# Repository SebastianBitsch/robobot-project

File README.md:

### Getting started

1. Connect to robot 
  ```bash
  ssh local@10.197.216.74
  ```

2. Login
  ```password: grenen```

3. Build
  ```bash
  cd svn/robobot/raubase/build && make
  ```

4. Run
  ```bash
  cd svn/robobot/raubase/build && ./raubase
  ```

### Tips and tricks
- Moving files from ```ssh``` to ```local```. On a terminal on your local machine: 
  ```bash
  scp -r local@10.197.216.74:/home/local/svn<PATH_TO_FILE> <LOCAL_PATH>
  ```
  - For instance:
  ```bash
  scp -r local@10.197.216.74:/home/local/svn/robobot/raubase/build/img/ /Users/sebastianbitsch/Desktop/
  ```

# Camera
Access the stream
```bash
cd svn/robobot/raubase/build/
motion
```
See the output stream at <http://10.197.216.74:8081>

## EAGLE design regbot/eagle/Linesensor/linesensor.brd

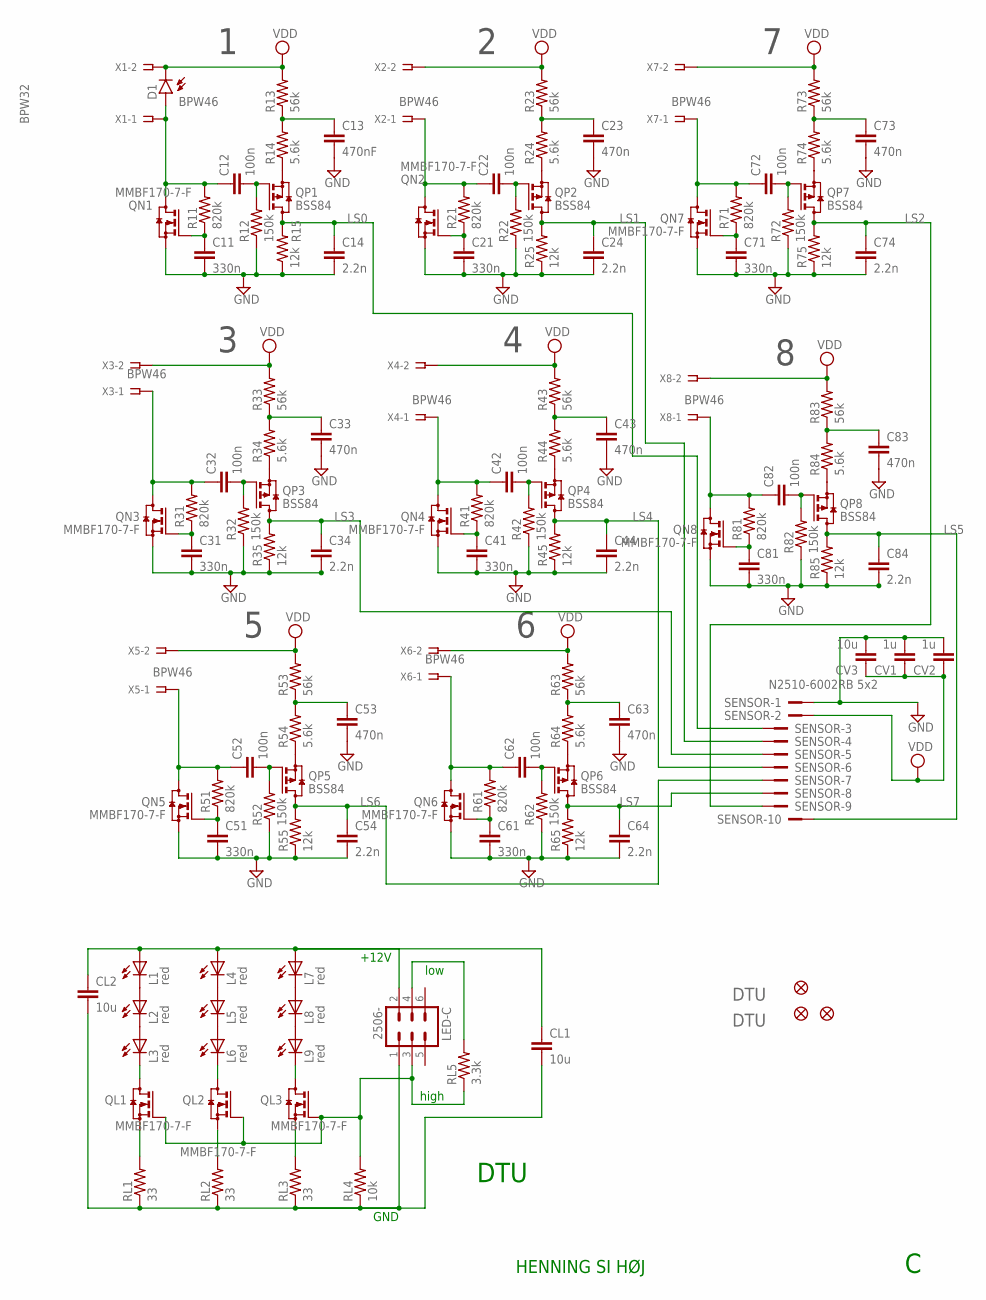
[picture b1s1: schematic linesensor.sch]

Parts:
C11, C21, C31, C41, C51, C61, C71, C81: 330n; 0805
C12, C22, C32, C42, C52, C62, C72, C82: 100n; 0805
C13: 470nF; 0805
C14, C24, C34, C44, C54, C64, C74, C84: 2.2n; 0805
C23, C33, C43, C53, C63, C73, C83: 470n; 0805
CL1, CL2: 10u; 1210
CV1, CV2: 1u; 0805
CV3: 10u; 1210
D1: BPW32
FD1, FD2, FD3: FIDUCIAL1X2; FIDUCIAL-1X2
L1, L2, L3, L4, L5, L6, L7, L8, L9: red; LED3MM
LED-C: 2506-; PAK100/2500-06
QL1, QL2, QL3: MMBF170-7-F; SOT23
QN1, QN2, QN3, QN4, QN5, QN6, QN7, QN8: MMBF170-7-F; SOT23
QP1, QP2, QP3, QP4, QP5, QP6, QP7, QP8: BSS84; SOT23
R11, R21, R31, R41, R51, R61, R71, R81: 820k; 0805
R12, R22, R32, R42, R52, R62, R72, R82: 150k; 0805
R13, R23, R33, R43, R53, R63, R73, R83: 56k; 0805
R14, R24, R34, R44, R54, R64, R74, R84: 5.6k; 0805
R15, R25, R35, R45, R55, R65, R75, R85: 12k; 0805
RL1, RL2, RL3: 33; 0805
RL4: 10k; 0805
RL5: 3.3k; 0805
SENSOR: N2510-6002RB 5x2; PAK100/2500-10
U$1: DTUSMALL-5MM; DTU-SMALL-5MM
U$2: DTULARGE; DTU-LARGE
X1, X2, X3, X4, X5, X6, X7, X8: BPW46; SSW-102-02-S-S

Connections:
GATE_CTRL: LED-C.3, QL1.1 (G), QL2.1 (G), QL3.1 (G), RL4.2, RL5.1
GND: C11.2, C13.2, C14.2, C21.2, C23.2, C24.2, C31.2, C33.2, C34.2, C41.2, C43.2, C44.2, C51.2, C53.2, C54.2, C61.2, C63.2, C64.2, C71.2, C73.2, C74.2, C81.2, C83.2, C84.2, CV1.2, CV2.2, CV3.2, QN1.2 (S), QN2.2 (S), QN3.2 (S), QN4.2 (S), QN5.2 (S), QN6.2 (S), QN7.2 (S), QN8.2 (S), R12.1, R15.1, R22.1, R25.1, R32.1, R35.1, R42.1, R45.1, R52.1, R55.1, R62.1, R65.1, R72.1, R75.1, R82.1, R85.1, SENSOR.1
GND2: CL1.2, CL2.2, LED-C.1, RL1.1, RL2.1, RL3.1, RL4.1
LS0: C14.1, QP1.3 (D), R15.2, SENSOR.3
LS1: C24.1, QP2.3 (D), R25.2, SENSOR.4
LS2: C74.1, QP7.3 (D), R75.2, SENSOR.9
LS3: C34.1, QP3.3 (D), R35.2, SENSOR.5
LS4: C44.1, QP4.3 (D), R45.2, SENSOR.6
LS5: C84.1, QP8.3 (D), R85.2, SENSOR.10
LS6: C54.1, QP5.3 (D), R55.2, SENSOR.7
LS7: C64.1, QP6.3 (D), R65.2, SENSOR.8
unnamed: QP1.2 (S), R14.1
unnamed: QP2.2 (S), R24.1
unnamed: C11.1, QN1.1 (G), R11.1
unnamed: C12.1, D1.A, QN1.3 (D), R11.2, X1.1
unnamed: C12.2, QP1.1 (G), R12.2
unnamed: L1.K (C), L2.A
unnamed: C13.1, R13.1, R14.2
unnamed: C21.1, QN2.1 (G), R21.1
unnamed: C22.1, QN2.3 (D), R21.2, X2.1
unnamed: C22.2, QP2.1 (G), R22.2
unnamed: L2.K (C), L3.A
unnamed: C23.1, R23.1, R24.2
unnamed: QP3.2 (S), R34.1
unnamed: C31.1, QN3.1 (G), R31.1
unnamed: C32.1, QN3.3 (D), R31.2, X3.1
unnamed: C32.2, QP3.1 (G), R32.2
unnamed: L4.K (C), L5.A
unnamed: C33.1, R33.1, R34.2
unnamed: QP4.2 (S), R44.1
unnamed: C41.1, QN4.1 (G), R41.1
unnamed: C42.1, QN4.3 (D), R41.2, X4.1
unnamed: C42.2, QP4.1 (G), R42.2
unnamed: L5.K (C), L6.A
unnamed: C43.1, R43.1, R44.2
unnamed: QP5.2 (S), R54.1
unnamed: C51.1, QN5.1 (G), R51.1
unnamed: C52.1, QN5.3 (D), R51.2, X5.1
unnamed: C52.2, QP5.1 (G), R52.2
unnamed: L7.K (C), L8.A
unnamed: C53.1, R53.1, R54.2
unnamed: QP6.2 (S), R64.1
unnamed: C61.1, QN6.1 (G), R61.1
unnamed: C62.1, QN6.3 (D), R61.2, X6.1
unnamed: C62.2, QP6.1 (G), R62.2
unnamed: L8.K (C), L9.A
unnamed: C63.1, R63.1, R64.2
unnamed: QP7.2 (S), R74.1
unnamed: C71.1, QN7.1 (G), R71.1
unnamed: C72.1, QN7.3 (D), R71.2, X7.1
unnamed: C72.2, QP7.1 (G), R72.2
unnamed: L3.K (C), QL1.3 (D)
unnamed: C73.1, R73.1, R74.2
unnamed: QP8.2 (S), R84.1
unnamed: C81.1, QN8.1 (G), R81.1
unnamed: C82.1, QN8.3 (D), R81.2, X8.1
unnamed: C82.2, QP8.1 (G), R82.2
unnamed: L6.K (C), QL2.3 (D)
unnamed: C83.1, R83.1, R84.2
unnamed: L9.K (C), QL3.3 (D)
unnamed: QL1.2 (S), RL1.2
unnamed: QL2.2 (S), RL2.2
unnamed: QL3.2 (S), RL3.2
unnamed: LED-C.4, RL5.2
VDD: CV1.1, CV2.1, CV3.1, D1.K (C), R13.2, R23.2, R33.2, R43.2, R53.2, R63.2, R73.2, R83.2, SENSOR.2, X1.2, X2.2, X3.2, X4.2, X5.2, X6.2, X7.2, X8.2
VDD2: CL1.1, CL2.1, L1.A, L4.A, L7.A, LED-C.2

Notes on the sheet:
DTU
HENNING SI HØJ
+12V
GND
low
high

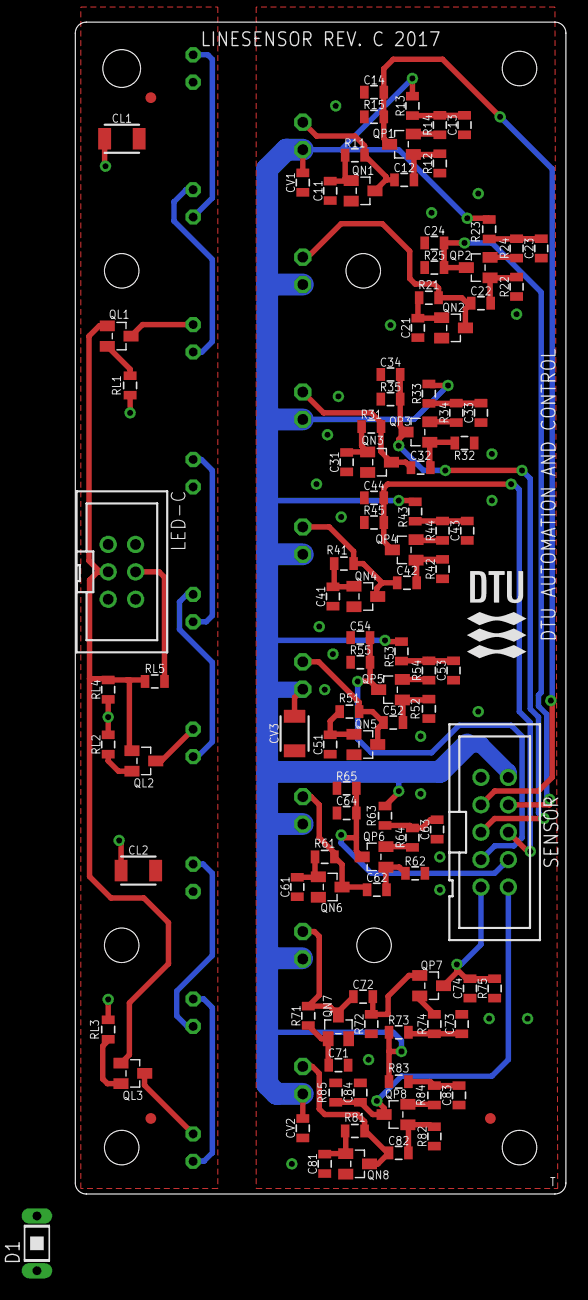
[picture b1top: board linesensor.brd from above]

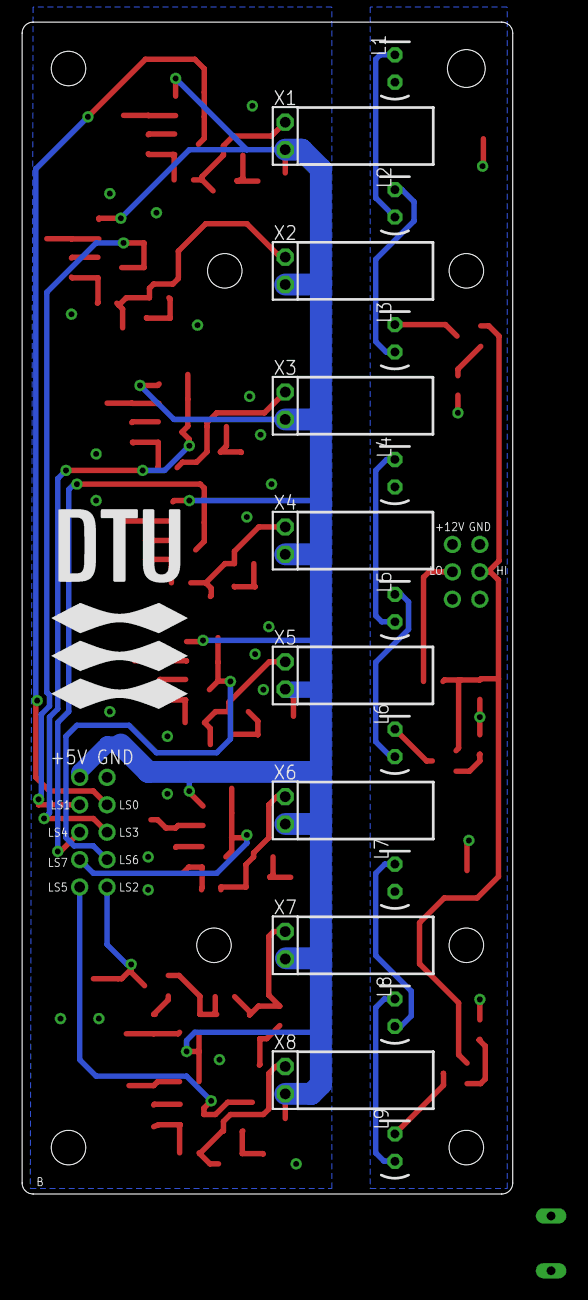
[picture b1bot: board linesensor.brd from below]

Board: 2 copper layers, 45.5 x 108.6 mm, 126 parts (18 on the bottom side), 66 nets.

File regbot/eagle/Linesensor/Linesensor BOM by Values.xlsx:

No. | part number/description | Package | Value | Qty | RefDefs | Note
1 |  | C0805 | 100nF/50V | 8 | C12, C22, C32, C42, C52, C62, C72, C82
2 |  | R0805 | 10k/1% | 1 | RL4
3 |  | C1210 | 10uF/50V | 3 | CL1, CL2, CV3
4 |  | R0805 | 12k/1% | 8 | R15, R25, R35, R45, R55, R65, R75, R85
5 |  | R0805 | 150k/1% | 8 | R12, R22, R32, R42, R52, R62, R72, R82
6 |  | C0805 | 1uF/50V | 2 | CV1, CV2
7 |  | C0805 | 2.2nF/50V | 8 | C14, C24, C34, C44, C54, C64, C74, C84
8 |  | R0805 | 3.3k/1% | 1 | RL5
9 |  | R0805 | 33R/1% | 3 | RL1, RL2, RL3
10 |  | C0805 | 330nF/50V | 8 | C11, C21, C31, C41, C51, C61, C71, C81
11 |  | C0805 | 470nF/50V | 8 | C13, C23, C33, C43, C53, C63, C73, C83
12 |  | R0805 | 5.6k/1% | 8 | R14, R24, R34, R44, R54, R64, R74, R84
13 |  | R0805 | 56k/1% | 8 | R13, R23, R33, R43, R53, R63, R73, R83
14 |  | R0805 | 820k/1% | 8 | R11, R21, R31, R41, R51, R61, R71, R81
15 |  | SOT23 | BSS84 | 8 | QP1, QP2, QP3, QP4, QP5, QP6, QP7, QP8
16 |  | SOT23 | MMBF170 | 11 | QL1, QL2, QL3, QN1, QN2, QN3, QN4, QN5, QN6, QN7, QN8
 | PCBWay PCB Assembly Service

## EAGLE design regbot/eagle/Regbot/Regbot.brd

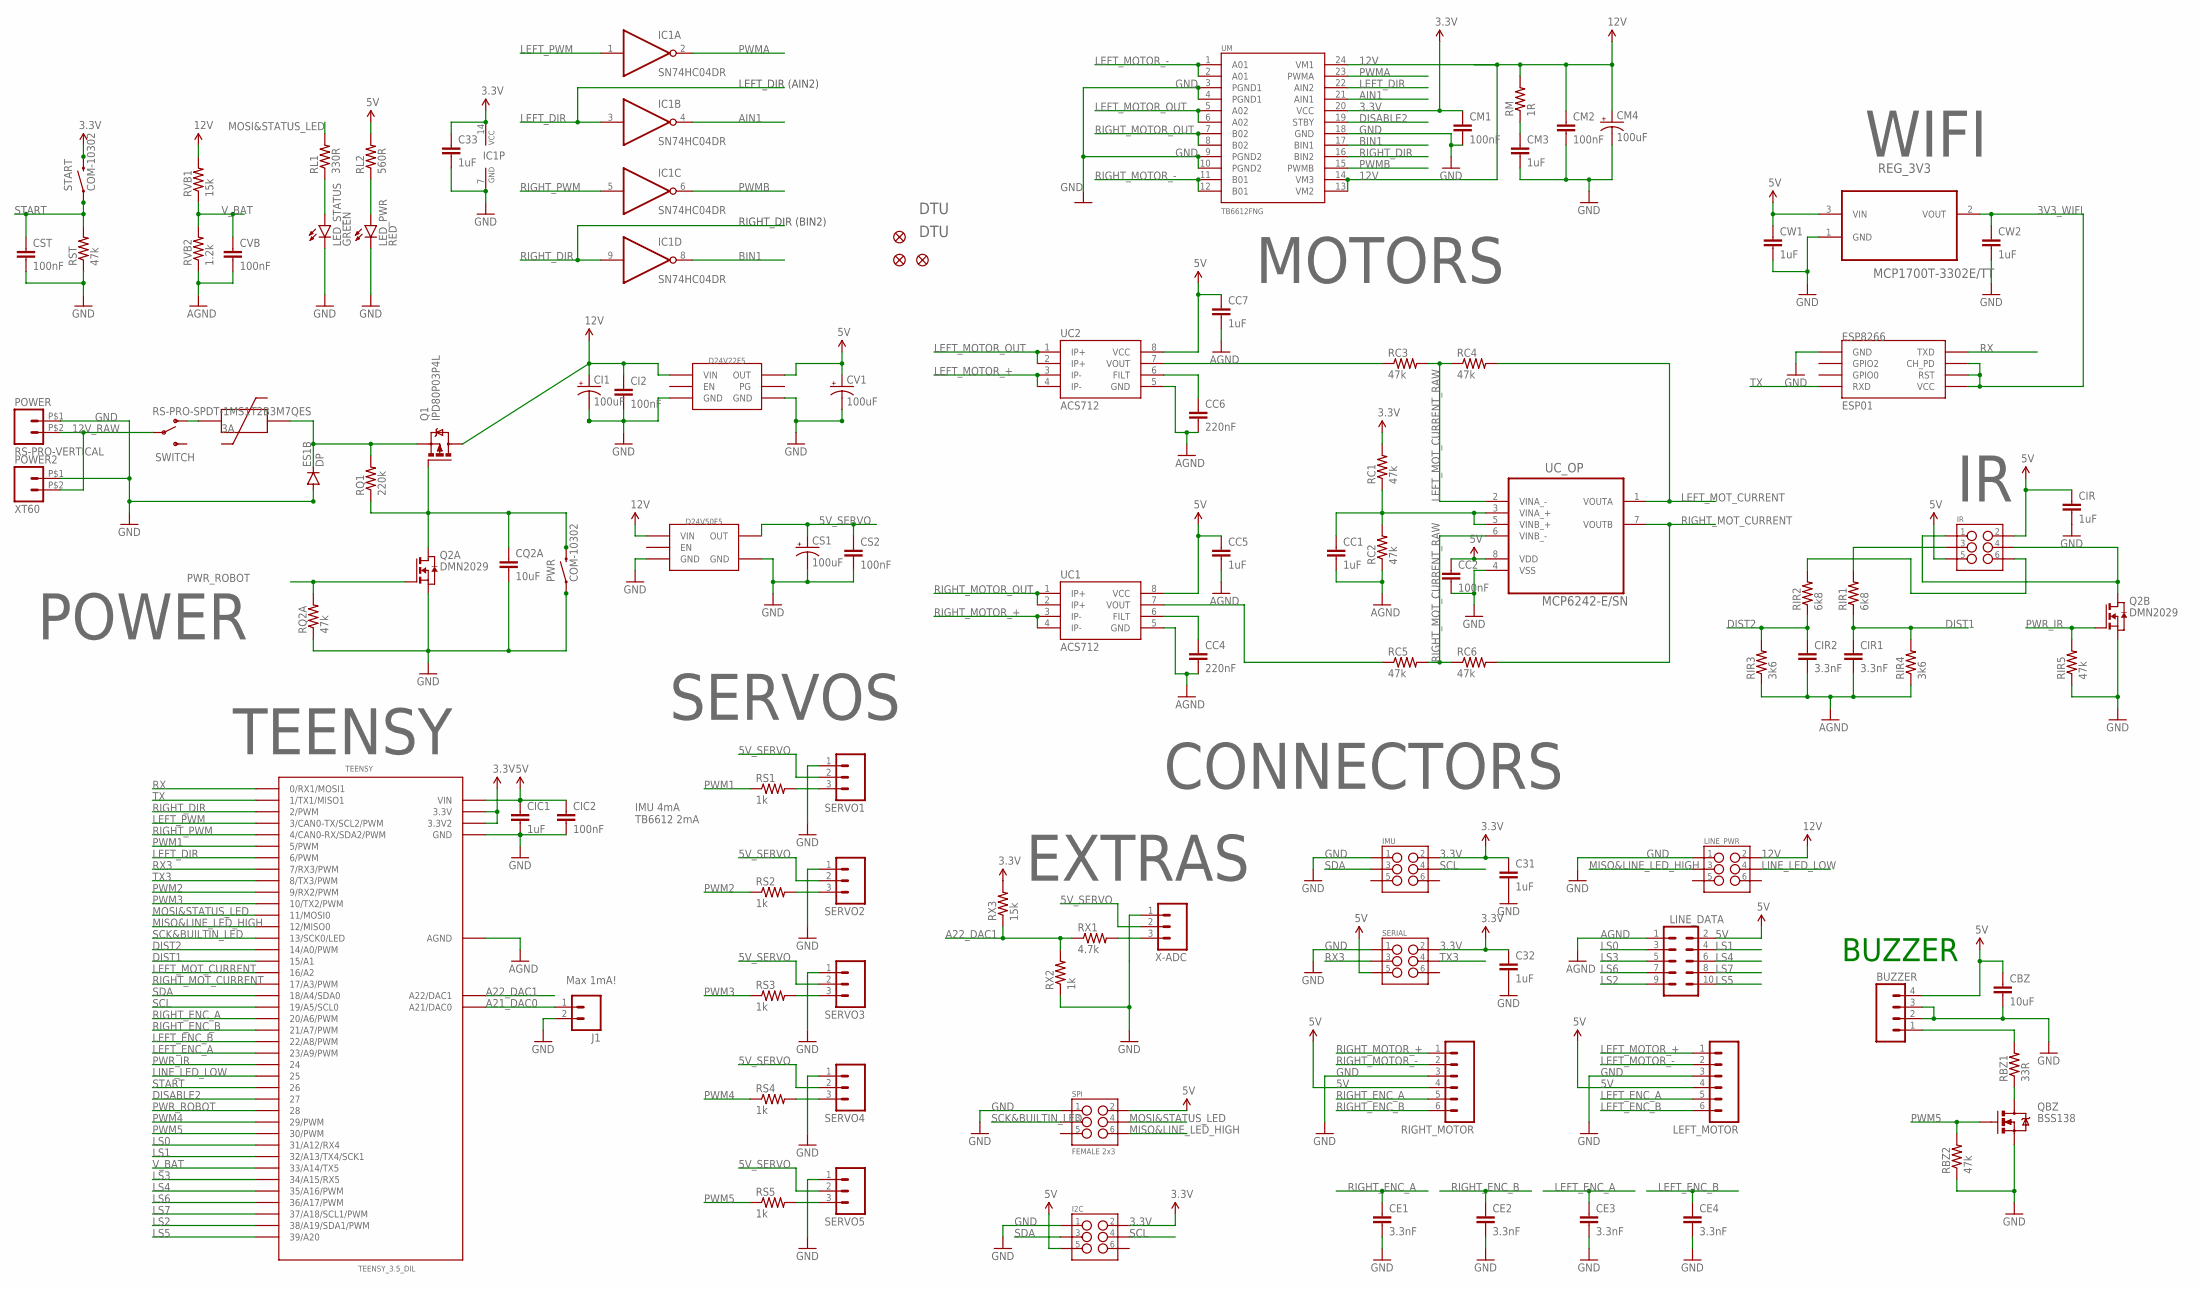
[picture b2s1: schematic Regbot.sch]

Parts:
BUZZER: M04POLAR; MOLEX-1X4
C31, C32, C33: 1uF; 0805
CBZ: 10uF; 1210
CC1, CC5, CC7: 1uF; 0805
CC2: 100nF; 0805
CC4, CC6: 220nF; 0805
CE1, CE2, CE3, CE4: 3.3nF; 0805
CI1: 100uF; PANASONIC_D_XL
CI2: 100nF; 0805
CIC1: 1uF; 0805
CIC2: 100nF; 0805
CIR: 1uF; 0805
CIR1, CIR2: 3.3nF; 0805
CM1, CM2: 100nF; 0805
CM3: 1uF; 0805
CM4: 100uF; PANASONIC_D_XL
CQ2A: 10uF; 1210
CS1: 100uF; PANASONIC_D_XL
CS2: 100nF; 0805
CST: 100nF; 0805
CV1: 100uF; PANASONIC_D_XL
CVB: 100nF; 0805
CW1, CW2: 1uF; 0805
D24V22F5: POLOLU_D24V22; D24V22
D24V50F5: POLOLU_D24V50; D24V50
DP: ES1B; SMA-DIODE
ESP8266: ESP01
FD1, FD2, FD3: FIDUCIAL1X2; FIDUCIAL-1X2
I2C: M03X2SHROUD; 2X3-SHROUDED
IC1: SN74HC04DR; SO14
IMU: M03X2SHROUD; 2X3-SHROUDED
IR: M03X2SHROUD; 2X3-SHROUDED
J1: M02PTH; 1X02
LED_PWR: RED; LED-1206
LED_STATUS: GREEN; LED-1206
LEFT_MOTOR: M06SILK_FEMALE_PTH; 1X06
LINE_DATA: M05X2SHD; 2X5-SHROUDED
LINE_PWR: M03X2SHROUD; 2X3-SHROUDED
MAIN_FUSE: SMF_OMNI-BLOK_FUSE_BLOCK
POWER: RS-PRO-VERTICAL
POWER2: XT60
PWR: COM-10302; TACTILE-PTH-12MM
Q1: IPD80P03P4L; D-PAK_TO252AA
Q2: DMN2029; SO8
QBZ: BSS138; SOT23
RBZ1: 33R; 0805
RBZ2: 47k; 0805
RC1, RC2, RC3, RC4, RC5, RC6: 47k; 0805
REG_3V3: MCP1700T-3302E/TT; SOT95P237X112-3N
RIGHT_MOTOR: M06SILK_FEMALE_PTH; 1X06
RIR1, RIR2: 6k8; 0805
RIR3, RIR4: 3k6; 0805
RIR5: 47k; 0805
RL1: 330R; 0805
RL2: 560R; 0805
RM: 1R; 0805
RQ1: 220k; 0805
RQ2A: 47k; 0805
RS1, RS2, RS3, RS4, RS5: 1k; 0805
RST: 47k; 0805
RVB1: 15k; 0805
RVB2: 1.2k; 0805
RX1: 4.7k; 0805
RX2: 1k; 0805
RX3: 15k; 0805
SERIAL: M03X2SHROUD; 2X3-SHROUDED
SERVO1, SERVO2, SERVO3, SERVO4, SERVO5: M03POLAR; MOLEX-1X3
SPI: FEMALE 2x3; 2X3
START: COM-10302; TACTILE-PTH-12MM
SWITCH: RS-PRO-SPDT-1MS1T2B3M7QES; RS-PRO-1MS1T2B3M7QES
TEENSY: TEENSY_3.5_DIL
U$1: DTUMEDIUM-9MM; DTU-MEDIUM-9MM
U$2: DTULARGE; DTU-LARGE
UC1, UC2: ACS712; SO08
UC_OP: MCP6242-E/SN; SOIC127P600X175-8N
UM: TB6612FNG; SSOP24
X-ADC: M03POLAR; MOLEX-1X3

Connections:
3.3V: C31.1, C32.1, C33.1, CM1.1, I2C.2, IC1.14 (VCC), IMU.2, RC1.2, RX3.2, SERIAL.2, START.3, START.4, TEENSY.3.3V, TEENSY.3.3V3 (3.3V2), UM.20 (VCC)
3V3_WIFI: CW2.1, ESP8266.CH_PD, ESP8266.RST, ESP8266.VCC, REG_3V3.2 (VOUT)
5V: BUZZER.4, CBZ.1, CC2.1, CC5.1, CC7.1, CIC1.1, CIC2.1, CIR.1, CV1.+, CW1.1, D24V22F5.P$OUT (OUT), I2C.5, IR.2, IR.5, LEFT_MOTOR.4, LINE_DATA.2, REG_3V3.3 (VIN), RIGHT_MOTOR.4, RL2.2, SERIAL.5, SPI.2, TEENSY.VIN, UC1.8 (VCC), UC2.8 (VCC), UC_OP.8 (VDD)
5V_SERVO: CS1.+, CS2.1, D24V50F5.P$OUT (OUT), SERVO1.2, SERVO2.2, SERVO3.2, SERVO4.2, SERVO5.2, X-ADC.2
12V: CI1.+, CI2.1, CM2.1, CM4.+, D24V22F5.P$VIN (VIN), D24V50F5.P$VIN (VIN), LINE_PWR.2, Q1.4 (D), RM.2, RVB1.2, UM.13 (VM2), UM.14 (VM3), UM.24 (VM1)
12V_RAW: POWER.P$2 (2), POWER2.P$2 (2), SWITCH.P$2 (P2)
A21_DAC0: J1.1, TEENSY.A21 (A21/DAC0)
A22_DAC1: RX1.1, RX2.2, RX3.1, TEENSY.A22 (A22/DAC1)
AGND: CC1.2, CC4.2, CC5.2, CC6.2, CC7.2, CIR1.2, CIR2.2, CVB.2, LINE_DATA.1, RC2.1, RIR3.1, RIR4.1, RVB2.1, TEENSY.AGND, UC1.5 (GND), UC2.5 (GND)
AIN1: IC1.4 (O), UM.21 (AIN1)
BIN1: IC1.8 (O), UM.17 (BIN1)
DISABLE2: TEENSY.27, UM.19 (STBY)
DIST1: CIR1.1, RIR1.1, RIR4.2, TEENSY.15/A1
DIST2: CIR2.1, RIR2.1, RIR3.2, TEENSY.14/A0 (14/A0/PWM)
GND: BUZZER.2, BUZZER.3, C31.2, C32.2, C33.2, CBZ.2, CC2.2, CE1.2, CE2.2, CE3.2, CE4.2, CI1.-, CI2.2, CIC1.2, CIC2.2, CIR.2, CM1.2, CM2.2, CM3.2, CM4.-, CQ2A.2, CS1.-, CS2.2, CST.2, CV1.-, CW1.2, CW2.2, D24V22F5.P$GND1 (GND), D24V22F5.P$GND2 (GND2), D24V50F5.P$GND (GND), D24V50F5.P$GND2 (GND2), DP.A, ESP8266.GND, I2C.1, IC1.7 (GND), IMU.1, J1.2, LED_PWR.C, LED_STATUS.C, LEFT_MOTOR.3, LINE_PWR.1, POWER.P$1 (1), POWER2.P$1 (1), PWR.1, PWR.2, Q2.1 (S), Q2.3 (S), QBZ.2 (S), RBZ2.1, REG_3V3.1 (GND), RIGHT_MOTOR.3, RIR5.1, RQ2A.1, RST.1, RX2.1, SERIAL.1, SERVO1.1, SERVO2.1, SERVO3.1, SERVO4.1, SERVO5.1, SPI.1, TEENSY.GND, TEENSY.GND1 (GND), UC_OP.4 (VSS), UM.3 (PGND1), UM.4 (PGND1), UM.9 (PGND2), UM.10 (PGND2), UM.18 (GND), X-ADC.1
LEFT_DIR: IC1.3 (I), TEENSY.6 (6/PWM), UM.22 (AIN2)
LEFT_ENC_A: CE3.1, LEFT_MOTOR.5, TEENSY.23/A9 (23/A9/PWM)
LEFT_ENC_B: CE4.1, LEFT_MOTOR.6, TEENSY.22/A8 (22/A8/PWM)
LEFT_MOTOR_+: LEFT_MOTOR.1, UC2.3 (IP-), UC2.4 (IP-)
LEFT_MOTOR_-: LEFT_MOTOR.2, UM.1 (A01), UM.2 (A01)
LEFT_MOTOR_OUT: UC2.1 (IP+), UC2.2 (IP+), UM.5 (A02), UM.6 (A02)
LEFT_MOT_CURRENT: RC4.2, TEENSY.16/A2, UC_OP.1 (VOUTA)
LEFT_MOT_CURRENT_RAW: RC3.2, RC4.1, UC_OP.2 (VINA_-)
LEFT_PWM: IC1.1 (I), TEENSY.3 (3/CAN0-TX/SCL2/PWM)
LINE_LED_LOW: LINE_PWR.4, TEENSY.25
LS0: LINE_DATA.3, TEENSY.31/A12 (31/A12/RX4)
LS1: LINE_DATA.4, TEENSY.32/A13 (32/A13/TX4/SCK1)
LS2: LINE_DATA.9, TEENSY.38/A19 (38/A19/SDA1/PWM)
LS3: LINE_DATA.5, TEENSY.34/A15 (34/A15/RX5)
LS4: LINE_DATA.6, TEENSY.35/A16 (35/A16/PWM)
LS5: LINE_DATA.10, TEENSY.39/A20
LS6: LINE_DATA.7, TEENSY.36/A17 (36/A17/PWM)
LS7: LINE_DATA.8, TEENSY.37/A18 (37/A18/SCL1/PWM)
MISO&LINE_LED_HIGH: LINE_PWR.3, SPI.6, TEENSY.12 (12/MISO0)
MOSI&STATUS_LED: RL1.2, SPI.4, TEENSY.11 (11/MOSI0)
unnamed: BUZZER.1, RBZ1.2
unnamed: QBZ.3 (D), RBZ1.1
unnamed: LED_STATUS.A, RL1.1
unnamed: LED_PWR.A, RL2.1
unnamed: DP.C, MAIN_FUSE.PIN1, Q1.3 (S), RQ1.2
unnamed: MAIN_FUSE.PIN2, SWITCH.P$1 (O1)
unnamed: CQ2A.1, PWR.3, PWR.4, Q1.1 (G), Q2.7 (D), Q2.8 (D), RQ1.1
unnamed: CM3.1, RM.1
unnamed: CC4.1, UC1.6 (FILT)
unnamed: CC6.1, UC2.6 (FILT)
unnamed: RC5.1, UC1.7 (VOUT)
unnamed: CC1.1, RC1.1, RC2.2, UC_OP.3 (VINA_+), UC_OP.5 (VINB_+)
unnamed: RC3.1, UC2.7 (VOUT)
unnamed: IR.1, IR.4, Q2.5 (D), Q2.6 (D)
unnamed: RS1.2, SERVO1.3
unnamed: IR.3, RIR1.2
unnamed: IR.6, RIR2.2
unnamed: RS2.2, SERVO2.3
unnamed: RS3.2, SERVO3.3
unnamed: RS4.2, SERVO4.3
unnamed: RS5.2, SERVO5.3
unnamed: RX1.2, X-ADC.3
PWM1: RS1.1, TEENSY.5 (5/PWM)
PWM2: RS2.1, TEENSY.9 (9/RX2/PWM)
PWM3: RS3.1, TEENSY.10 (10/TX2/PWM)
PWM4: RS4.1, TEENSY.29 (29/PWM)
PWM5: QBZ.1 (G), RBZ2.2, RS5.1, TEENSY.30 (30/PWM)
PWMA: IC1.2 (O), UM.23 (PWMA)
PWMB: IC1.6 (O), UM.15 (PWMB)
PWR_IR: Q2.4 (G), RIR5.2, TEENSY.24
PWR_ROBOT: Q2.2 (G), RQ2A.2, TEENSY.28
RIGHT_DIR: IC1.9 (I), TEENSY.2 (2/PWM), UM.16 (BIN2)
RIGHT_ENC_A: CE1.1, RIGHT_MOTOR.5, TEENSY.20/A6 (20/A6/PWM)
RIGHT_ENC_B: CE2.1, RIGHT_MOTOR.6, TEENSY.21/A7 (21/A7/PWM)
RIGHT_MOTOR_+: RIGHT_MOTOR.1, UC1.3 (IP-), UC1.4 (IP-)
RIGHT_MOTOR_-: RIGHT_MOTOR.2, UM.11 (B01), UM.12 (B01)
RIGHT_MOTOR_OUT: UC1.1 (IP+), UC1.2 (IP+), UM.7 (B02), UM.8 (B02)
RIGHT_MOT_CURRENT: RC6.2, TEENSY.17/A3 (17/A3/PWM), UC_OP.7 (VOUTB)
RIGHT_MOT_CURRENT_RAW: RC5.2, RC6.1, UC_OP.6 (VINB_-)
RIGHT_PWM: IC1.5 (I), TEENSY.4 (4/CAN0-RX/SDA2/PWM)
RX: ESP8266.TX (TXD), TEENSY.0 (0/RX1/MOSI1)
RX3: SERIAL.3, TEENSY.7 (7/RX3/PWM)
SCK&BUILTIN_LED: SPI.3, TEENSY.13 (13/SCK0/LED)
SCL: I2C.4, IMU.4, TEENSY.19/A5 (19/A5/SCL0)
SDA: I2C.3, IMU.3, TEENSY.18/A4 (18/A4/SDA0)
START: CST.1, RST.2, START.1, START.2, TEENSY.26
TX: ESP8266.RX (RXD), TEENSY.1 (1/TX1/MISO1)
TX3: SERIAL.4, TEENSY.8 (8/TX3/PWM)
V_BAT: CVB.1, RVB1.1, RVB2.2, TEENSY.33/A14 (33/A14/TX5)

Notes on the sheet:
LEFT_DIR (AIN2)
RIGHT_DIR (BIN2)
MOTORS
WIFI
SERVOS
EXTRAS
CONNECTORS
IMU 4mA TB6612 2mA
POWER
TEENSY
BUZZER
Max 1mA!

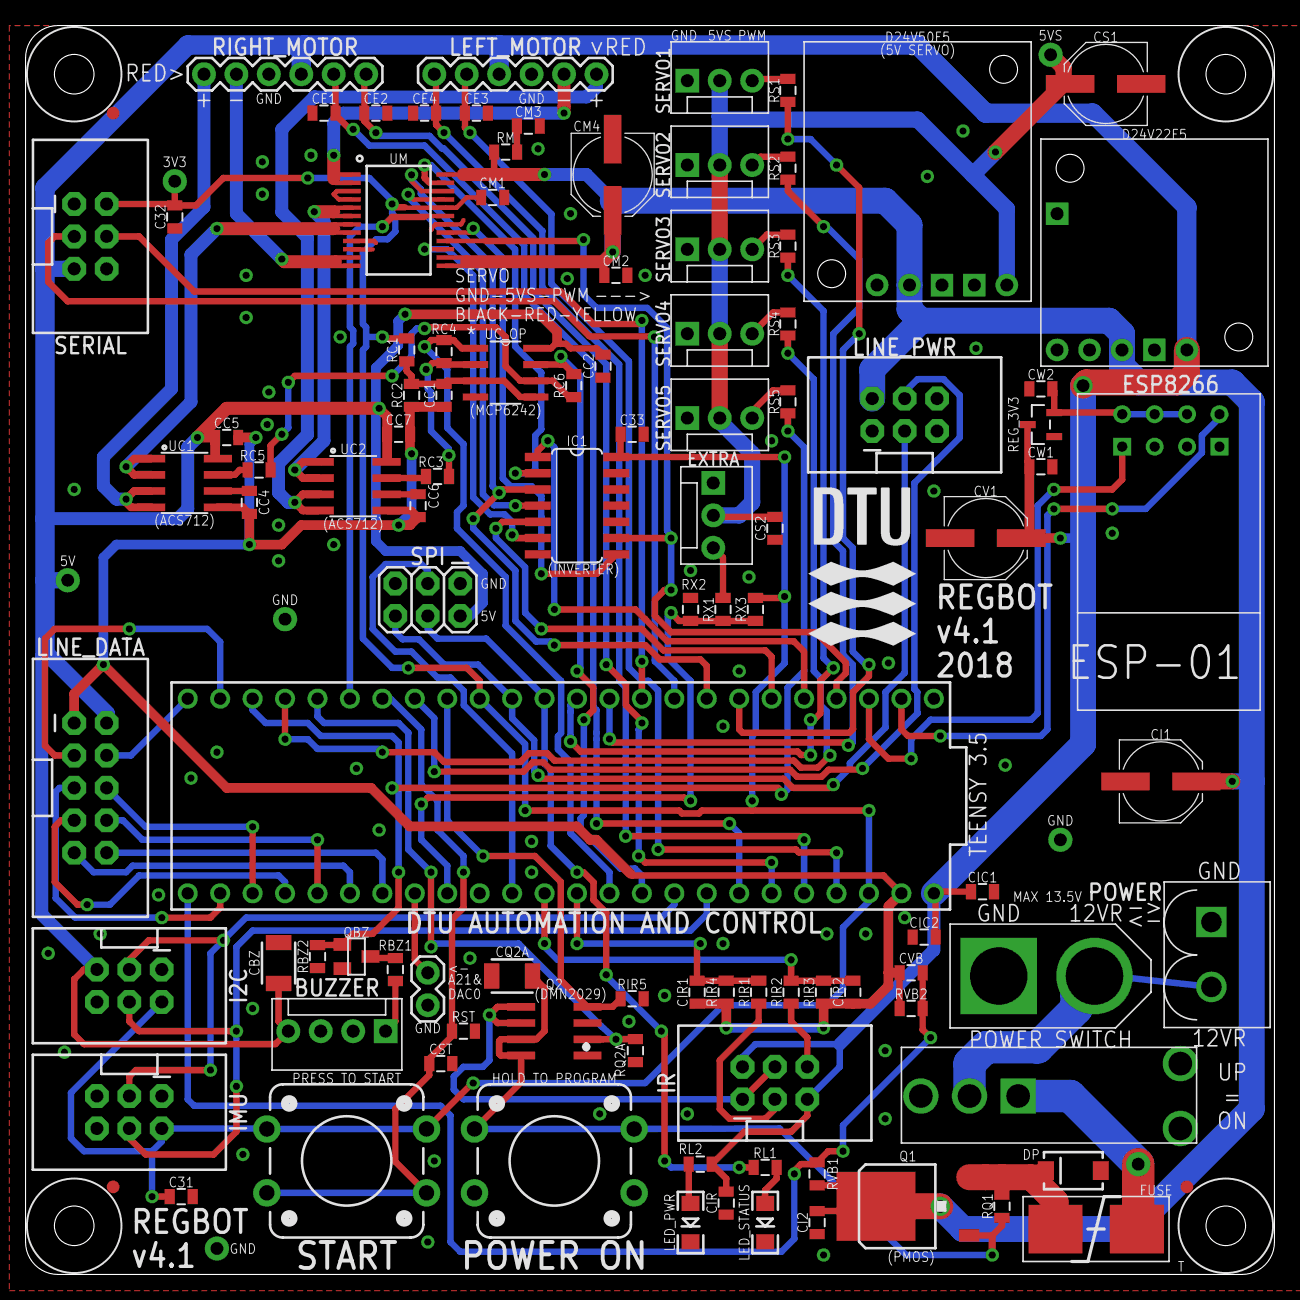
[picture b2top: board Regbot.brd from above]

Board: 2 copper layers, 97.8 x 97.8 mm, 106 parts (1 on the bottom side), 84 nets.

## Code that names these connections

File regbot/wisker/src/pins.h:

#ifndef PINS_H
#define PINS_H

// REGBOT_HW4 will be defined in makefile, if Teensy 3.5 is selected.

#define OLD_PIN_LINE_LED        32 // For version < 3
#define OLD_PIN_START_BUTTON    11 // For version 1

// Pin defines for Regbot v3 and older

#ifndef REGBOT_HW4

// Main pins
#define PIN_LED_DEBUG           13 // (LED_BUILTIN)
#define PIN_START_BUTTON        6
#define PIN_LINE_LED_HIGH       18
#define PIN_LINE_LED_LOW        25
#define PIN_DISABLE2            11
#define PIN_POWER_IR            32
#define PIN_POWER_ROBOT         33

// ADC pins
#define ADC_NUM_NO_LS           5
#define ADC_NUM_ALL             (ADC_NUM_NO_LS + 8)
#define PIN_IR_RAW_1            A1
#define PIN_IR_RAW_2            A0
#define PIN_BATTERY_VOLTAGE     A9
#define PIN_LEFT_MOTOR_CURRENT  A10
#define PIN_RIGHT_MOTOR_CURRENT A11
#define PIN_LINE_SENSOR_0       A12
#define PIN_LINE_SENSOR_1       A13
#define PIN_LINE_SENSOR_2       A15   // A19
#define PIN_LINE_SENSOR_3       A16   // A15
#define PIN_LINE_SENSOR_4       A17   // A16
#define PIN_LINE_SENSOR_5       A18   // A20
#define PIN_LINE_SENSOR_6       A19   // A17
#define PIN_LINE_SENSOR_7       A20   // A18

// Motor Controller pins
#define PIN_LEFT_DIR            2
#define PIN_LEFT_PWM            3
#define PIN_RIGHT_PWM           4
#define PIN_RIGHT_DIR           12
#define PIN_LEFT_ENCODER_A      20
#define PIN_LEFT_ENCODER_B      19
#define PIN_RIGHT_ENCODER_A     22
#define PIN_RIGHT_ENCODER_B     21
#define M1DIR           PIN_LEFT_DIR // M1IN2 - Teensy Digital 2 (direction)
#define M1PWM           PIN_LEFT_PWM // M1IN1 - Teensy Digital 3 (PWM)
#define M2DIR3          PIN_RIGHT_DIR // M2IN2 - Teensy Digital 8 (direction) hardware 3 only
#define M2PWM3          PIN_RIGHT_PWM // M2IN1 - Teensy Digital 4 (PWM) hardware 3
#define M12DIS          PIN_DISABLE2 // M1+M2 D2  enable both motors - hardware 3 only
#define M1ENC_A         PIN_LEFT_ENCODER_A // Encoder A - Teensy Digital 20
#define M1ENC_B         PIN_LEFT_ENCODER_B // Encoder B - Teensy Digital 19
#define M2ENC_A         PIN_RIGHT_ENCODER_A // Encoder A - Teensy Digital 22
#define M2ENC_B         PIN_RIGHT_ENCODER_B // Encoder B - Teensy Digital 21
// Legacy pins (only used < 3)
#define M1DIS1          4 // M1D2  - Teensy Digital 4 (disable (hiz))) - hardware < 3
#define M2DIS1          10 // M2D2  - Teensy Digital 10 (disable (hi-z)) - hardware < 3
#define M2PWM1          9 // M2IN1 - Teensy Digital 9 (PWM) hardware < 3
#define SLEW            7 // SLEW  - Teensy Digital 7  -  hardware 1 og 2 only, hardware 3 fixed high
#define M2DIR1          8 // M2IN2 - Teensy Digital 8 (direction) hardware < 3 only

// Servo pins
#define PIN_SERVO1      5 // Teensy pin for servo 1
#define PIN_SERVO2      9 // Teensy pin for servo 2 - not valid on version 3.0 or earlier (used for motor enable)
#define PIN_SERVO3      10 // Teensy pin for servo 3 - not valid on version 3.0 or earlier (used for motor enable)
#define SERVO_PIN_0     A14 // IO pin on servo board
#define SERVO_PIN_1     24  // IO pin on servo board

//////////////////////////////////////////////////////////////////////////////////////////////////////////////////////
//////////////////////////////////////////////////////////////////////////////////////////////////////////////////////
//////////////////////////////////////////////////////////////////////////////////////////////////////////////////////

// Pin Definitions for Regbot v4.1 2018
#elif defined(REGBOT_HW4)

// Main pins
#define PIN_LED_STATUS          11
#define PIN_LED_DEBUG           13
#define PIN_START_BUTTON        26
#define PIN_LINE_LED_HIGH       12
#define PIN_LINE_LED_LOW        25
#define PIN_DISABLE2            27
#define PIN_POWER_IR            24
#define PIN_POWER_ROBOT         28

// ADC pins
#define ADC_NUM_NO_LS           5
#define ADC_NUM_ALL             (ADC_NUM_NO_LS + 8)
//
#define PIN_IR_RAW_1            A1
#define PIN_IR_RAW_2            A0
#define PIN_BATTERY_VOLTAGE     A14
#define PIN_LEFT_MOTOR_CURRENT  A2
#define PIN_RIGHT_MOTOR_CURRENT A3
//
#define PIN_LINE_SENSOR_0       A12
#define PIN_LINE_SENSOR_1       A13
#define PIN_LINE_SENSOR_2       A15
#define PIN_LINE_SENSOR_3       A16
#define PIN_LINE_SENSOR_4       A17
#define PIN_LINE_SENSOR_5       A18
#define PIN_LINE_SENSOR_6       A19
#define PIN_LINE_SENSOR_7       A20

// Motor Controller pins
#define PIN_LEFT_DIR            6
#define PIN_LEFT_PWM            3
#define PIN_RIGHT_PWM           4
#define PIN_RIGHT_DIR           2

#define PIN_LEFT_ENCODER_A      23
#define PIN_LEFT_ENCODER_B      22
#define PIN_RIGHT_ENCODER_A     20
#define PIN_RIGHT_ENCODER_B     21
#define M1DIR           PIN_LEFT_DIR // M1IN2 - Teensy Digital (direction)
#define M1PWM           PIN_LEFT_PWM // M1IN1 - Teensy Digital (PWM)
#define M2DIR3          PIN_RIGHT_DIR // M2IN2 - Teensy Digital (direction) hardware 3 only
#define M2PWM3          PIN_RIGHT_PWM // M2IN1 - Teensy Digital (PWM) hardware 3
#define M12DIS          PIN_DISABLE2 // M1+M2 D2  enable both motors - hardware 3 only
#define M1ENC_A         PIN_LEFT_ENCODER_A // Encoder A - Teensy Digital
#define M1ENC_B         PIN_LEFT_ENCODER_B // Encoder B - Teensy Digital
#define M2ENC_A         PIN_RIGHT_ENCODER_A // Encoder A - Teensy Digital
#define M2ENC_B         PIN_RIGHT_ENCODER_B // Encoder B - Teensy Digital
// Legacy pins (only used < 3)
#define M1DIS1          4 // M1D2  - Teensy Digital 4 (disable (hiz))) - hardware < 3
#define M2DIS1          10 // M2D2  - Teensy Digital 10 (disable (hi-z)) - hardware < 3
#define M2PWM1          9 // M2IN1 - Teensy Digital 9 (PWM) hardware < 3
#define SLEW            7 // SLEW  - Teensy Digital 7  -  hardware 1 og 2 only, hardware 3 fixed high
#define M2DIR1          8 // M2IN2 - Teensy Digital 8 (direction) hardware < 3 only

// Servo pins
#define PIN_SERVO1      5 // Teensy pin for servo 1
#define PIN_SERVO2      9 // Teensy pin for servo 2
#define PIN_SERVO3      10 // Teensy pin for servo 3
#define PIN_SERVO4      29 // Teensy pin for servo 4
#define PIN_SERVO5      30 // Teensy pin for servo 5 (Shared with Buzzer!)
#define SERVO_PIN_0     PIN_SERVO4 // Deprecated!
#define SERVO_PIN_1     PIN_SERVO5 // Deprecated!
#define PIN_BUZZER		30 // Shared with SERVO5!

#endif

#endif

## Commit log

2024-02-02 entire robot code base
2024-02-14 testing
2024-02-14 added some comment of what to do
2024-02-16 added regbot
2024-02-16 more files
2024-02-16 removed logs etc.
2024-02-23 main vel test
2024-02-23 ignore ds
2024-02-23 template plan for golf
2024-02-23 include robot.ini
2024-02-23 changed 100 to 200 a lot of places
2024-02-23 comments
2024-02-23 added robot.ini
2024-02-23 stuff
2024-03-08 some control stuff
2024-03-08 goto
2024-03-08 some work
2024-03-14 linemode
2024-03-15 line offset
2024-03-15 disable line mode

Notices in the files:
parts and their libraries:
SparkFun-Resistors: Licensing: Creative Commons ShareAlike 4.0 International - https://creativecommons.org/licenses/by-sa/4.0
SparkFun-Passives: Licensing: CC v3.0 Share-Alike You are welcome to use this library for commercial purposes.
